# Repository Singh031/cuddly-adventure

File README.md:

# cuddly-adventure
Aquest projecte consisteix en el disseny i construcció d'un coet, tant del hardware com del software!

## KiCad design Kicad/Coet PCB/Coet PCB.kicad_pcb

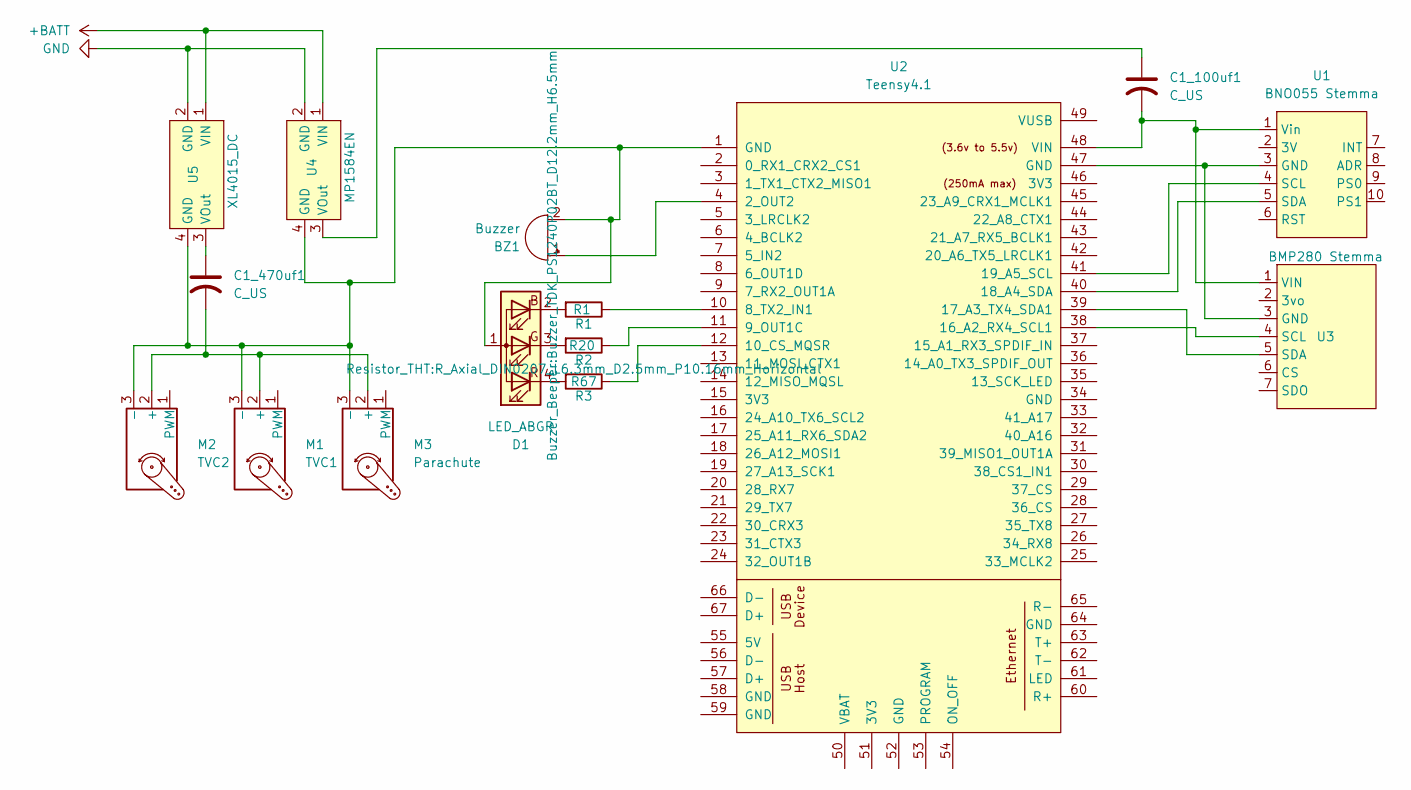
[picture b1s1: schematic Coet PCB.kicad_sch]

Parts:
BZ1: Buzzer; Buzzer_TDK_PS1240P02BT_D12.2mm_H6.5mm
C1_100uf1, C1_470uf1: C_US; CP_Elec_8x5.4
D1: LED_ABGR; LED_D5.0mm-4_RGB_Wide_Pins
M1: TVC1; PinHeader_1x03_P1.00mm_Vertical
M2: TVC2; PinHeader_1x03_P1.00mm_Vertical
M3: Parachute; PinHeader_1x03_P1.00mm_Vertical
R1: R1; R_Axial_DIN0207_L6.3mm_D2.5mm_P10.16mm_Horizontal
R2: R20; R_Axial_DIN0207_L6.3mm_D2.5mm_P10.16mm_Horizontal
R3: R67; R_Axial_DIN0207_L6.3mm_D2.5mm_P10.16mm_Horizontal
U1: BNO055 Stemma; BNO055
U2: Teensy4.1; Teensy41
U3: BMP280 Stemma; BMP280
U4: MP1584EN
U5: XL4015_DC; XL4015 DC-DC

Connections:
+BATT: U4.1 (VIN), U5.1 (VIN)
GND: U4.2 (GND), U5.2 (GND)
unnamed: BZ1.1 (+), U2.4 (2_OUT2)
unnamed: BZ1.2 (-), D1.1 (A), M1.3 (-), M2.3 (-), M3.3 (-), U2.1 (GND), U4.4 (GND), U5.4 (GND)
unnamed: D1.2 (BK), R1.2
unnamed: D1.3 (GK), R2.2
unnamed: D1.4 (RK), R3.2
unnamed: C1_470uf1.2, M1.2 (+), M2.2 (+), M3.2 (+)
unnamed: U1.3 (GND), U2.47 (GND)
unnamed: U1.4 (SCL), U2.41 (19_A5_SCL)
unnamed: U1.5 (SDA), U2.40 (18_A4_SDA)
unnamed: C1_100uf1.2, U1.1 (Vin), U2.48 (VIN)
unnamed: R1.1, U2.10 (8_TX2_IN1)
unnamed: R2.1, U2.11 (9_OUT1C)
unnamed: R3.1, U2.12 (10_CS_MQSR)
unnamed: C1_100uf1.1, U4.3 (VOut)
unnamed: C1_470uf1.1, U5.3 (VOut)

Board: 2 copper layers, 15 parts (0 on the bottom side), 17 nets, no tracks yet.

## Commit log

2026-04-14 S'han afegir els primers arxius
2026-04-14 S'han afegit els primers arxius
2026-04-15 kicad components
2026-04-15 Added the next libraries to Kicad: Teensy4.1, Bno055, Bmp280, MP1584EN, XL4015DC
2026-04-15 Prova
2026-04-16 He acabat les conecions del esquema!
